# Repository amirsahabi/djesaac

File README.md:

# DJESAAC

## About

This is a small web app designed to take music requests from users and play a lightshow
controlled by an arduino along to the music

## Installation

### Server

The server is written in python and depends on the libraries
[flask](http://flask.pocoo.org/), [peewee](https://pypi.python.org/pypi/peewee),
[numpy](http://www.numpy.org/),
[requests](http://docs.python-requests.org/en/master/),
[youtube_dl](https://pypi.python.org/pypi/youtube_dl), 
[pyfirmata](https://pypi.python.org/pypi/pyFirmata), [pygame](https://www.pygame.org), 
[pysoundfile](https://pysoundfile.readthedocs.io/en/0.9.0/) and [pydub](https://pypi.python.org/pypi/pydub) 
(all of which are available to install through pip). youtube_dl and pydub also rely on [ffmpeg](https://ffmpeg.org/)
which can be installed on OS X through brew, on linux through your favorite package manager.

### Arduino

The Arduino Uno may be programmed through the Arduino IDE (v1.6.3). The sketch StandardFirmata.ino is available in the IDE under  File>Examples>Firmata>StandardFirmata (The sketch is also provided in this repository under Arduino>StandardFirmata.ino). As documented in app>constants.py the pin configuration uses three PWM digital output pins.

### Board

The current iteration of the PCB is posted in the repository under Hardware>Board>djesaac.sch. A .brd file is included for manufacturing.
Parts needed for this circuit are as follows:

3 x 2N3904 Transistors,
3 x 330 Ohm 1/4 Watt Resistors,
9 x 180 Ohm 1 Watt Resistors,
2 x 4 by 1 Headers,
1 x 2 by 1 Headers,

Parts are assembled according to labeling. 180 Ohm resistors are placed across the two rows of 9 through-holes.
Functionality has been tested with an Arduino Uno and [WenTop LED Strip](https://www.amazon.com/gp/product/B00X7JUN0I/ref=od_aui_detailpages00?ie=UTF8&psc=1)

## How to Run

From the app folder, start the server from a command line with the following command
```
$ python app.py
```

The servers default location is at port 3000 so you can navigate in a browser to
localhost:3000 to be sure the server is up and running

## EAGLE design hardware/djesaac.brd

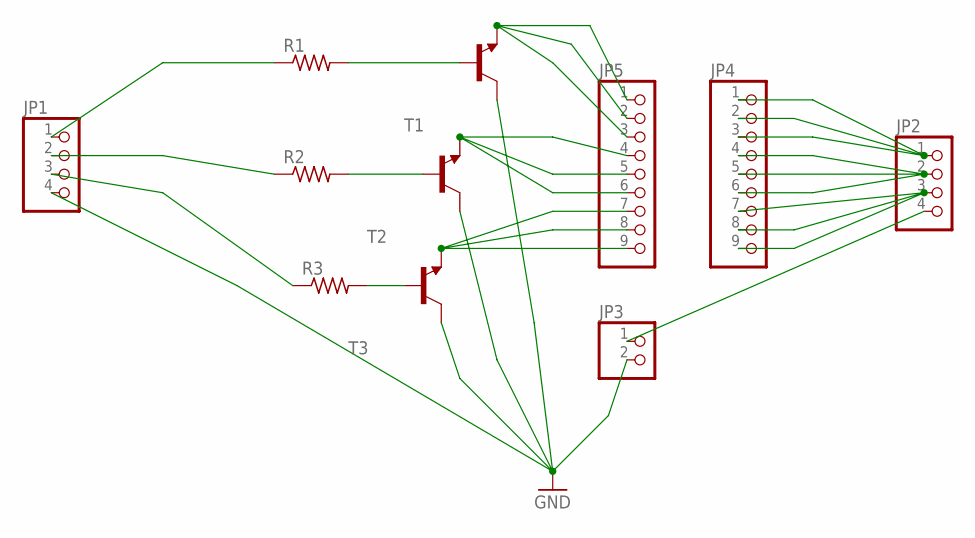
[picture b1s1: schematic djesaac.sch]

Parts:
JP1, JP2: PINHD-1X4; 1X04
JP3: PINHD-1X2; 1X02
JP4, JP5: PINHD-1X9; 1X09
R1, R2, R3: R-US_0207/10; 0207/10
T1, T2, T3: -NPN-TO92-CBE; TO92-CBE

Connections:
GND: JP1.4, JP3.2, T1.C, T2.C, T3.C
unnamed: JP1.1, R1.1
unnamed: JP1.2, R2.1
unnamed: JP1.3, R3.1
unnamed: JP2.4, JP3.1
unnamed: R1.2, T1.B
unnamed: R2.2, T2.B
unnamed: R3.2, T3.B
unnamed: JP5.1, JP5.2, JP5.3, T1.E
unnamed: JP5.4, JP5.5, JP5.6, T2.E
unnamed: JP5.7, JP5.8, JP5.9, T3.E
unnamed: JP2.1, JP4.1, JP4.2, JP4.3
unnamed: JP2.2, JP4.4, JP4.5, JP4.6
unnamed: JP2.3, JP4.7, JP4.8, JP4.9

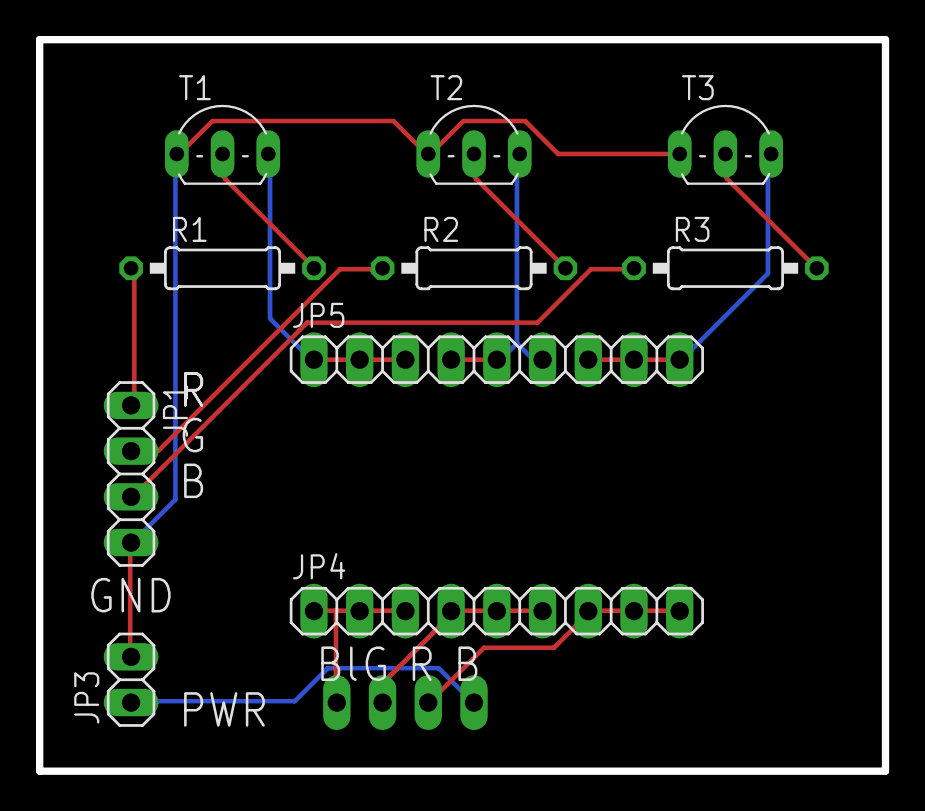
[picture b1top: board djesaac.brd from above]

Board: 2 copper layers, 47.0 x 40.6 mm, 11 parts (1 on the bottom side), 14 nets.

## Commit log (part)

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2017-04-02 First commit!
2017-04-02 Added skeleton to the server
2017-04-02 Added a cool css stylesheet for a table I found online, added more to the app, added a database class, and added two extremely rough html files for the home, and the add pages
2017-04-02 adding git ignore, also adding more features to app.py, changes to the css table, adding history.html file
2017-04-02 improve database classes to include a history table (for recent history of songs played), and a queue table (songs up on deck). also added djezak.m matlab script for reference
2017-04-02 added more functionality to the app, added jquery and a javascript file to operate the /add path
2017-04-02 added more JS functionality to the add page, got the table to load with songs on deck on the home page
2017-04-02 fixed indexing issue in song listing
2017-04-03 Fixed some issues with download location and cleaned up html template file
2017-04-03 fixed the history html file and the function
2017-04-03 Revert "Testing First Commit"
    This reverts commit 4751507b02375832e77a0d1eac4a7d08081c34ef.
2017-04-03 Server now downloads songs as .wav files (tested on Linux, don't know if it works for other OS) also included sample .wav song in music folder
2017-04-03 Added a basic readme
2017-04-03 Adding utility.py to process .wav files and write rgb data to Arduino
2017-04-03 Added R/G/B value calculation and song playback
2017-04-04 Shit works yo
2017-04-04 Okay it's actually done now
2017-04-04 add trying to connect to arduino on mac
2017-04-04 Fixed frequency issue, also some thresholding stuff. Still needs work with silence in beginning of songs.
2017-04-04 Removed songstart sample counter in attempt to remedy asynchronous activity in songs with long soundless intros
2017-04-04 Fixed Humble bug. Soundless intros now cause no asynchronous activity.
2017-04-05 Added a replay button to the history page
2017-04-05 README.md edited online with Bitbucket
2017-04-05 Fixed some indexing things in translation from matlab to python, also removed a few print statements
2017-04-06 Issue #3: Now able to remove songs from the queue
2017-04-06 Added .db file to gitignore
2017-04-06 Remove header replay
2017-04-06 Add wav files to the gitignore
2017-04-06 Adding styling. To do: Fix buttons, add song page/module
2017-04-06 Issue #8: Standby mode enabled when queue is empty
2017-04-06 Forgot a colon. Sorry, new to python.
2017-04-06 Issue #8: fix some class member function issues
2017-04-06 Indent issue fix for #8
2017-04-06 Standby Mode is operational. Cycles between 3 patterns.
2017-04-06 Play/stop icon under "Currently Playing" works now
2017-04-06 My bad, accidentally deleted the delete button. ANYWAYS, changed the icon
2017-04-06 Issue #11: change musicIsPlaying variable from string to boolean for page
2017-04-06 Debug mode doesn't spawn two threads anymore (ty Amir). Reload button. Other stylistic changes.
2017-04-06 Moved frequency processing to preprocess function. Look into adding preprocessing to eliminate silence between songs
2017-04-06 Fixed scrolling issues. And something else I can't remember.
2017-04-06 Fixed variable error
2017-04-07 Issue #2: Auto determine frequency binning before assigning values to led value arrays
2017-04-07 Issue #15: Move preprocessing into separate preprocessor class, extends thread TODO: preprocess future songs
2017-04-07 Fixed a misplaced 0 in version merge.
2017-04-07 Implemented Issue #15: Songs are preprocessed well before songs begin to play for seamlessness
2017-04-07 accidentally oopsed a letter
2017-04-07 Fixed some thread safety concerns with the preprocessor
2017-04-07 MultiThread implementation of preprocessor
    This is a multithread implementation of the song preprocessor. There is
    an issue with python's GIL that makes it not a true multithreaded
    application. I created this in a separate branch because I'm not
    entirely sure how appropriate it would be to push to master. Potential
    also for creating a multiPROCESS app.
2017-04-07 Put DBMonitor and Preprocessor into their own process, they are still threaded within that process
2017-04-07 Added some comments
2017-04-07 Issue #19: Resolved issue in preprocessing; argmax of empty array
2017-04-07 Styled add module
2017-04-07 Issue #19: Resolved issue in preprocessing; argmax of empty array (copy of 274e651)
2017-04-08 Fixed some interaction with issues with shared memory object
2017-04-08 Issue #14: changed cursor to use pointer over buttons
2017-04-08 Issue #12: Implemented next button
2017-04-08 Issue #22: Implemented a song listener to provide ServerSideEvents (SSE) when a song has finished playing
2017-04-08 Fixed an edge case for the SSE updater
2017-04-08 Fix infinite refreshing page when queue is empty
2017-04-08 Issue #23: Remove GET request access from /add/
2017-04-08 Add event listener to history page so history page reloads when song finishes
2017-04-08 Thought I commited this, i guess not
2017-04-08 Rearranged some import statements, moved utility.py into reference
2017-04-08 Issue #26: Jsonify the home page's post responses (not add)
2017-04-08 Issue #26: Jsonify history page responses
2017-04-08 Add dynamic rearranging to the playlist, no more page reloads for the hompage!!!
2017-04-08 Clean up some comments from the last commit
2017-04-08 One more javascript cleanup
2017-04-08 Just kidding this is the last one
2017-04-08 Added dynamic table updating for the history page
2017-04-08 Looks like when i added the utility.py file to reference, i forgot to remove it from the app folder.
2017-04-08 Quit the mixer when the song is over, for some reason I was having playback issues (playing the song at different speeds), and this seems to have resolved it
2017-04-08 fix edge case bug
2017-04-09 Issue #28: djesaac.db deleted online with Bitbucket
2017-04-09 turned pin writing into it's own function, little more intuitive now
2017-04-09 Issue #24: global variables file constants.py created and hardcoded strings in code have been replaced
2017-04-09 Issue #13: Thresholded LED values locally in time. Added intensity factor for quiet audible melodies based on logarithmic ratio of the maximum power to the relative local power. Also, preallocated la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
2017-04-09 More constants changing
2017-04-09 More constants stuff
2017-04-09 100th commit: add timestamp to song when it's finished preprocessing to see how long it's taken
2017-04-09 Fix link reassignment issue in home page
2017-04-10 Issue #31: Fixed divide by zero error with some if statement checks
2017-04-12 Fix some stupid bugs i made without testing
2017-04-12 More constants replacements
2017-04-12 Condition fix for entering standby mode
2017-04-12 window_size_sec needs to be an int
2017-04-13 FINALLY FIXED COLOR ISSUE
2017-04-13 Fixed #32: History now recounts correctly
2017-04-13 Issue #33: Quick fix for songs that have less than 2 channels of audio
2017-04-25 Added a missing constant for the Ubuntu default location for arduinos
2017-04-25 Remove deprecated add.html template
2017-04-27 Fixed #2: server no longer sends next message when pressing play from song being stoped
2017-04-27 Can add song by pressing ENTER now
2017-04-27 typo
2017-04-29 Changed design for navigation and adding song. I think this is a better UX - let me know your thoughts.
2017-04-29 Issue #4: Added backend variables for being able to realtime change latency, port location and pin locations
2017-04-29 Issue #4: Added more to the backend for settings page, needs front end implementation now
2017-04-29 Issue #4: Fixed an uninitialization error
2017-04-29 Fixed issue #7
2017-04-29 Issue #4: Last fix for the backend stuff due to some negligence on my part
2017-04-29 Issue #4: Fix logic
2017-04-29 Issue #5: UI updates when song has been added
2017-04-29 Issue #5: fix typo
2017-04-29 Added .idea folder to .gitignore
2017-04-29 When browser width changes, margins change. When width is really low, nav links turn into icons.
2017-04-29 Added same changes from 2df8492 to history page
2017-04-30 Issue #5: Redid everything so that it uses database queries and keeps track of connections, add and next work, still need to do removes
2017-04-30 Fixed #5: Realtime events now occur
2017-04-30 Fixed a lot of code styling things
2017-04-30 Removes add_suc alert when new song is added. Also cleared input field.
2017-04-30 Weird safari styling width fixed
2017-05-01 More code styling fixes
2017-05-01 Added Arduino information
2017-05-01 Add StandardFirmata.ino to repository
2017-05-01 Moved StandardFirmata.ino to arduino folder
2017-05-02 Fixed board initialization and standby mode typos
2017-05-02 Issue #9: add some more specific exceptions to try/catches
2017-05-04 Fixed trying to access led arrays with floats and improved standby
2017-05-04 Fixed $12: Can replay song more than once
2017-05-04 Fixed #12: Can replay song more than once
2017-05-04 Removed "Links" column because of space. Song titles are now also links to song source.
2017-05-05 Fix typo in readme
2017-05-05 For Issue #6, added play/stop event to ActionHistory so that playing and stopping is synced across all open browsers
2017-05-05 Added more responsive design. Fixed nav vertical alignment issues.
2017-05-05 Fixed #13
2017-05-05 Forgot to remove link column in /history
2017-05-05 Forgot to make nav changes on /history as well ...
2017-05-10 Re-enable submit button after successful submission
2017-05-10 Issue #11, now use .ogg files instead of .wav files to transition to being able to pause songs
2017-05-10 Fixed Issue #11 : Songs now pause (instead of stop) when hitting pause button
2017-05-10 Quick fixes and cleanup
2017-05-10 Update Readme to include pysoundfile module requirement
2017-05-10 Remove unnecessary import statements
2017-05-10 Remove Scipy lib req from Readme
2017-05-10 Update UI when sending replay request
2017-05-10 Fixed actual updating issue from history page
2017-05-15 Issue #14: Add entry point to autoplay music in settings. Also add shared variable for communication between dbmonitor and main app
2017-05-15 Forgot response data input
2017-05-17 Issue #4: Started work on an overlay dialog for settings
2017-05-17 Added centering for the button because I just figured out how
2017-05-17 Moved youtubedl functions into song_utilities for cleaner access.
2017-05-17 Issue #14: begin autoplaying music
2017-05-17 Fixed decoding failure
2017-05-18 Just making the settings dialog cleaner.
2017-05-18 Beginning to add some unit-testing stuff
2017-05-18 Added more unit testing
2017-05-18 Minor changes to last unit test changes
2017-05-18 Adding settings to history page
2017-05-18 Issue #15: Add unit testing for settings post
2017-05-18 Issue #15: More unit tests for settings page
2017-05-18 Added to enhancement #4 by giving visual confirmation when saving settings.
2017-05-19 Settings acts like a "link" so that it can utilize the pointer cursor.
2017-05-19 Issue #15: Settings unit test fixes
2017-05-19 Issue #15: Create unit tests for databases.py
2017-05-19 Issue #15: Finished databases.py unit tests
2017-05-19 Add a requirements.txt file for easy pip install
2017-05-19 Fix typo in requirements.txt
2017-05-19 Added numpy and requests to requirements
2017-05-19 Fixed issue with failing test
2017-05-19 Fixed the whole issue with killing the app
2017-05-19 Revert "Fixed the whole issue with killing the app" THIS DID NOT WORK This reverts commit 95acbfadc465faaf573f0e9e69ea8d8a6c4ac6ca.
2017-05-19 Fixed history alert alignments. Added hover affects to nav links.
2017-05-19 Adding more to #8: More mobile friendly
2017-05-20 Footer
2017-05-22 Issue #18: Fix remove button
2017-05-23 Fixed issue #16 - width of first column of playlist is defined.
2017-05-23 Change to footer: "Check us out on Github" is a link
2017-05-26 Fixed #18: songs can be removed when first added and link now shows up
2017-05-30 Small code cleanups and add to gitignore
2017-06-06 Remove reference folder, no longer relevant
2017-06-07 Small addition to unit tests
2017-06-07 Issue #6: Include song length in database for ticker to use
2017-06-11 Added a 'data structure' to keep the songs in, not complete yet but it's there. also added ticker css file
2017-06-11 Allow real time updates to affect songs[]
2017-06-11 Added checks on autoplay feature to see if songs have been played before
2017-06-12 Added Board info in Readme
2017-06-12 Commas
2017-06-12 hardware folder
2017-06-12 Added Eagle files
2017-06-16 Added link to jsfiddle in ticker.css
